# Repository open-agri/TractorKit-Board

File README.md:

# TractorKit-Board
The TractorKit board (KiCAD project)

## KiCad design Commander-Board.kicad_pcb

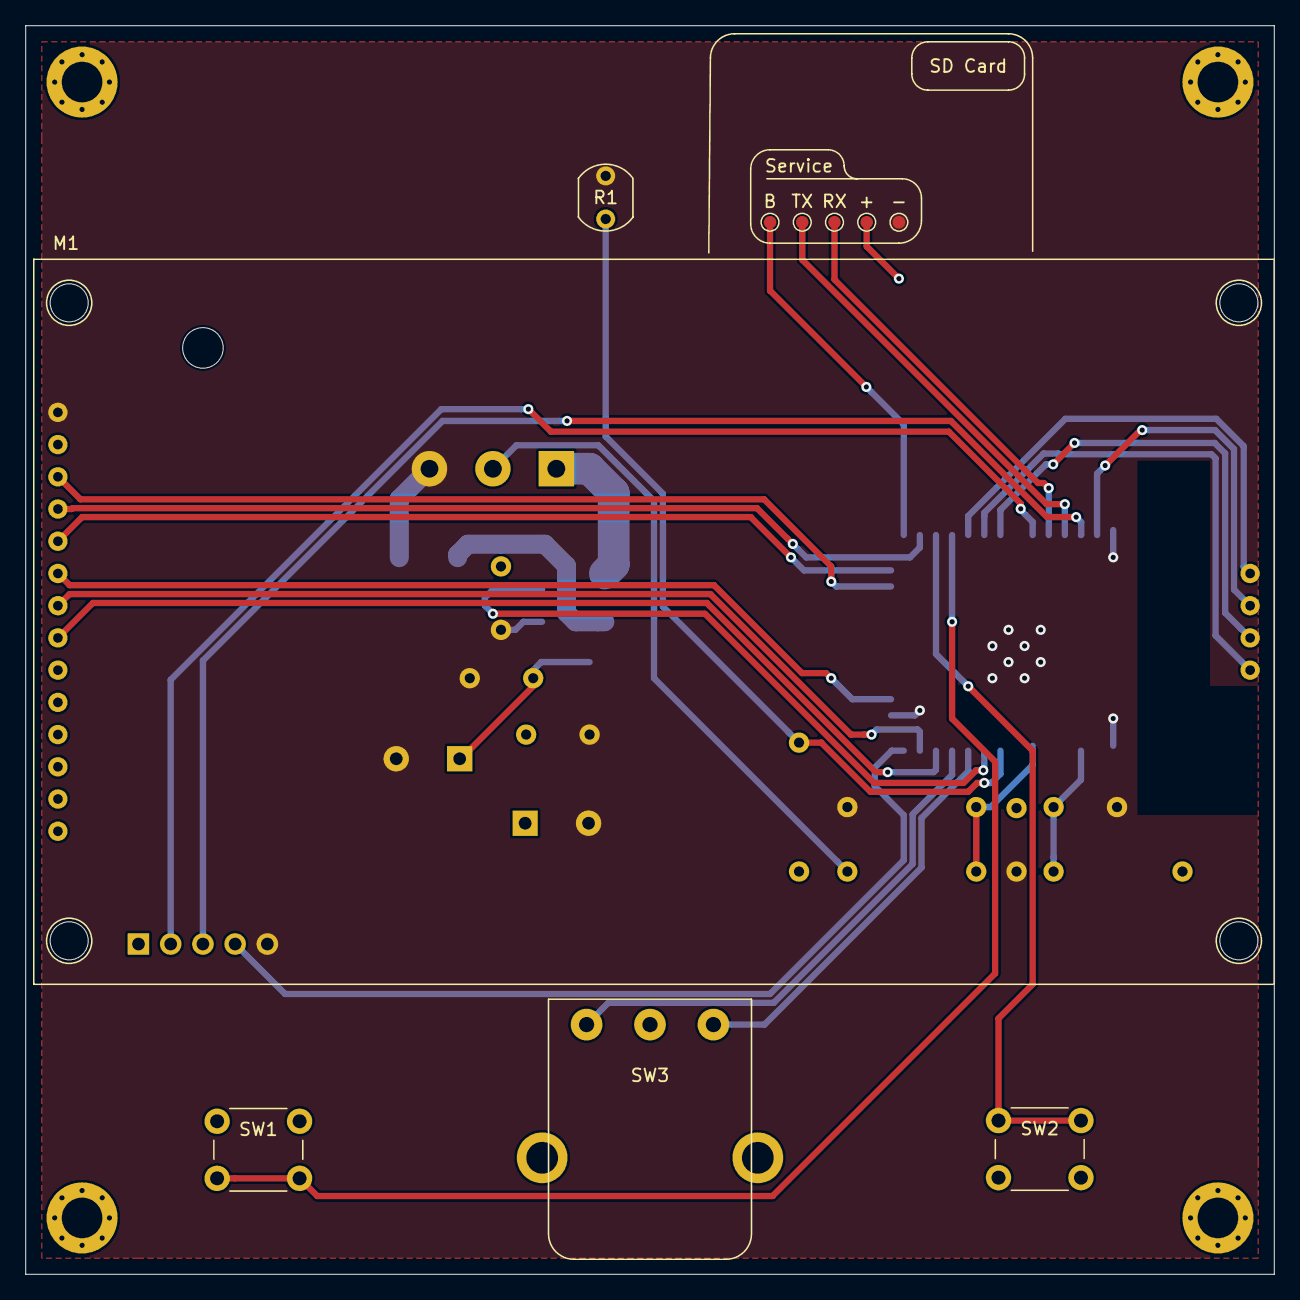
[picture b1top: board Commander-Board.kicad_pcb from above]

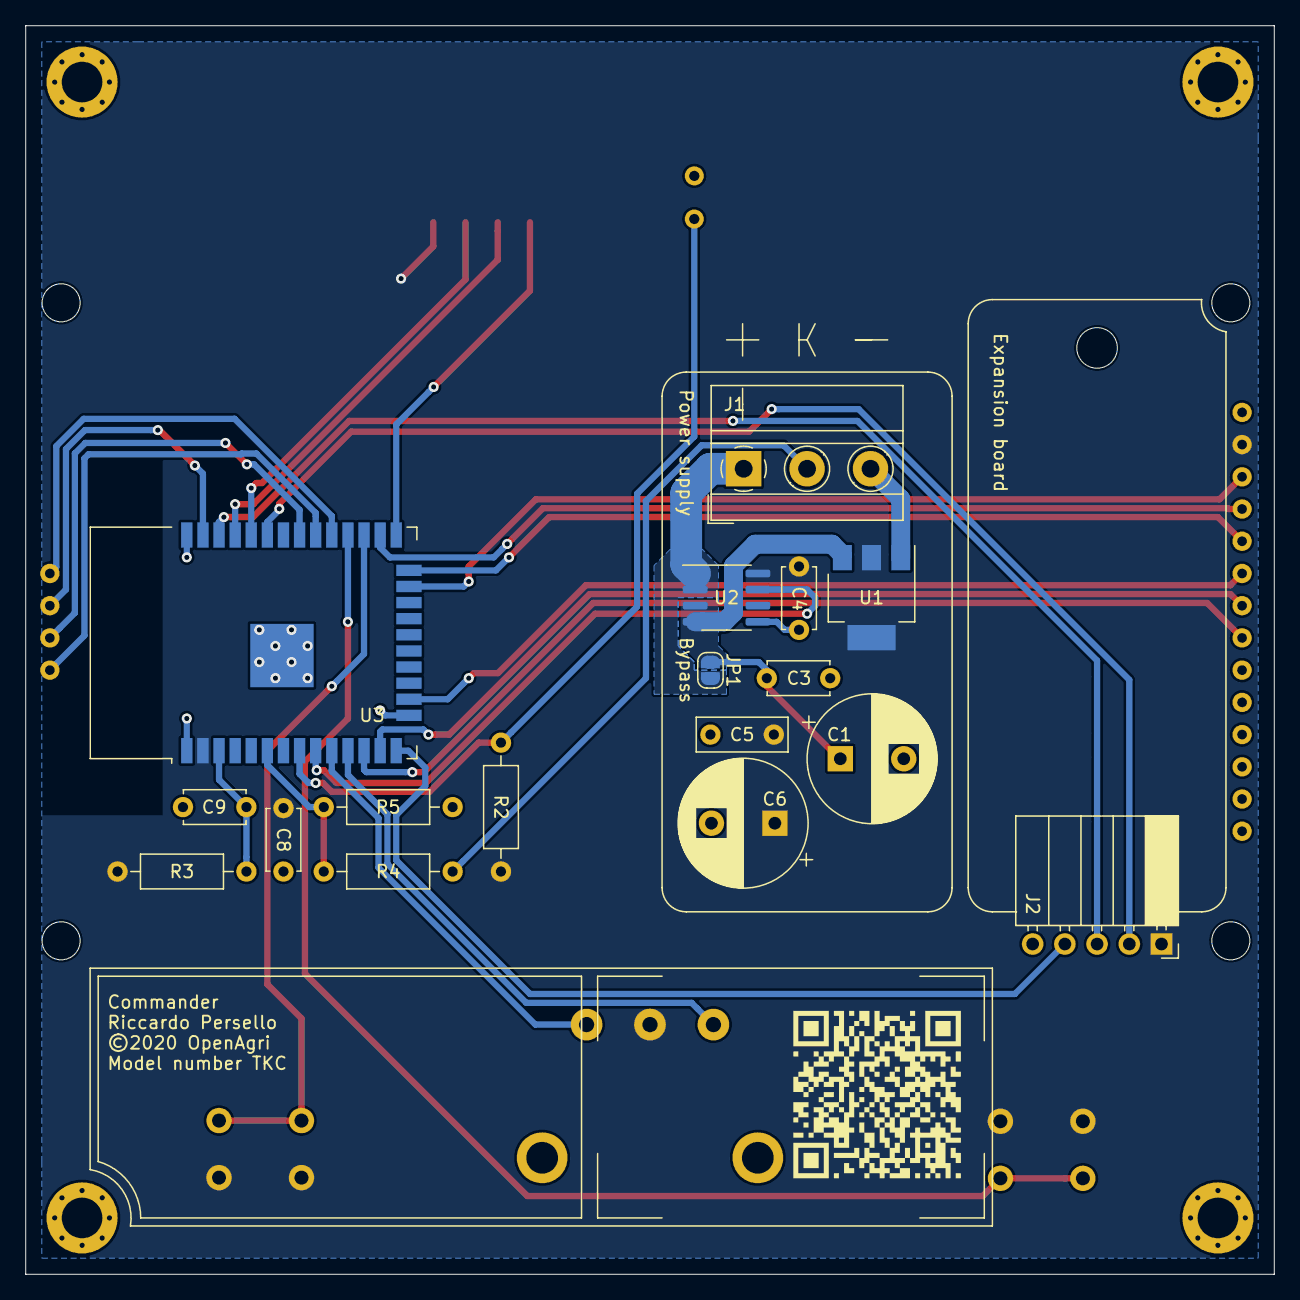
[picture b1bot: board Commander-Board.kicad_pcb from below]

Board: 2 copper layers, 98.4 x 98.4 mm, 33 parts (18 on the bottom side), 29 nets.

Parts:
 : MountingHole_3.2mm_M3_DIN965_Pad
 #2,  #3,  #4: MountingHole_3.2mm_M3_DIN965_Pad
 #5: QRCODE
 #6: MountingHole_3.2mm_M3
+: SERVICE_3V3; TestPoint_Pad_D1.0mm
-: SERVICE_GND; TestPoint_Pad_D1.0mm
B: SERVICE_BOOT; TestPoint_Pad_D1.0mm
C1: 100u; CP_Radial_D10.0mm_P5.00mm
C3: 1u; C_Disc_D4.7mm_W2.5mm_P5.00mm
C4, C9: 100n; C_Disc_D4.7mm_W2.5mm_P5.00mm
C5: 2.2u; C_Disc_D7.0mm_W2.5mm_P5.00mm
C6: 220u; CP_Radial_D10.0mm_P5.00mm
C8: C; C_Disc_D4.7mm_W2.5mm_P5.00mm
J1: POWER; TerminalBlock_MetzConnect_Type011_RT05503HBWC_1x03_P5.00mm_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
J2: EXPAND; PinSocket_1x05_P2.54mm_Horizontal
JP1: BYPASS; SolderJumper-2_P1.3mm_Open_RoundedPad1.0x1.5mm
M1: 3.5_TFT_SPI_480_320
R1: LDR; R_LDR_5.1x4.3mm_P3.4mm_Vertical
R2, R5: 1k; R_Axial_DIN0207_L6.3mm_D2.5mm_P10.16mm_Horizontal
R3, R4: 10k; R_Axial_DIN0207_L6.3mm_D2.5mm_P10.16mm_Horizontal
RX: SERVICE_RX; TestPoint_Pad_D1.0mm
SW1: BUTTON_BACK; SW_PUSH_6mm_H4.3mm
SW2: BUTTON_ENTER; SW_PUSH_6mm_H4.3mm
SW3: Rotary_Encoder; RotaryEncoder_Alps_EC16B04
TX: SERVICE_TX; TestPoint_Pad_D1.0mm
U1: AMS1117-3.3; SOT-223-3_TabPin2
U2: ACS711xLCTR-12AB; SOIC-8_3.9x4.9mm_P1.27mm
U3: ESP32-WROOM-32

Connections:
+3V3: +.1, C4.1, C5.1, C6.1, C8.1, J2.1, M1.13, R2.2, R3.1, SW1.1, SW2.2, SW3.C, U1.2, U2.8, U3.2
+12V: C1.1, C3.1, JP1.1, U1.3, U2.3, U2.4
/AN_CURR: U2.7, U3.9
/AN_LIGHT: R1.1, R2.1, U3.8
/AN_VOLT: R4.2, R5.1, U3.6
/ENC_A: SW3.A, U3.10
/ENC_B: SW3.B, U3.11
/EX_1: J2.2, U3.33
/EX_2: J2.3, U3.36
/EX_3: J2.4, U3.14
/PB_BACK: SW1.2, U3.28
/PB_ENT: SW2.1, U3.27
/PR_BOOT: B.1, U3.25
/PR_RX: RX.1, U3.34
/PR_TX: TX.1, U3.35
/SD_CS: M1.15, U3.29
/SD_MISO: M1.17, U3.31
/SD_MOSI: M1.16, U3.37
/SD_SCK: M1.18, U3.30
/TFT_BL: M1.7, U3.12
/TFT_CS: M1.12, U3.23
/TFT_DI: M1.9, U3.16
/TFT_RS: M1.10, U3.24
/TFT_RST: M1.11, U3.26
/TFT_SCK: M1.8, U3.13
GND: -.1, C1.2, C3.2, C4.2, C5.2, C6.2, C8.2, C9.1, J1.3, J2.5, M1.14, R1.2, R5.2, U1.1, U2.5, U3.1, U3.15, U3.38, U3.39
unnamed: C9.2, R3.2, U3.3
unnamed: J1.1, JP1.2, U2.1, U2.2
unnamed: J1.2, R4.1

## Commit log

2020-05-04 KiCAD Project
2020-05-09 Added components on board.
2020-05-10 Connections between devices.
2020-07-08 First schematic
2020-07-09 First board test
2020-07-21 Complete
2020-07-21 Minor fixes
2020-07-21 Minor corrections
2020-07-23 Added service labels
2020-07-26 New holes, removed board S/N.
2020-07-29 New service connector
2020-07-30 Ready for panelization.

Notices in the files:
Commander-Board.kicad_pcb:
©2020 OpenAgri
